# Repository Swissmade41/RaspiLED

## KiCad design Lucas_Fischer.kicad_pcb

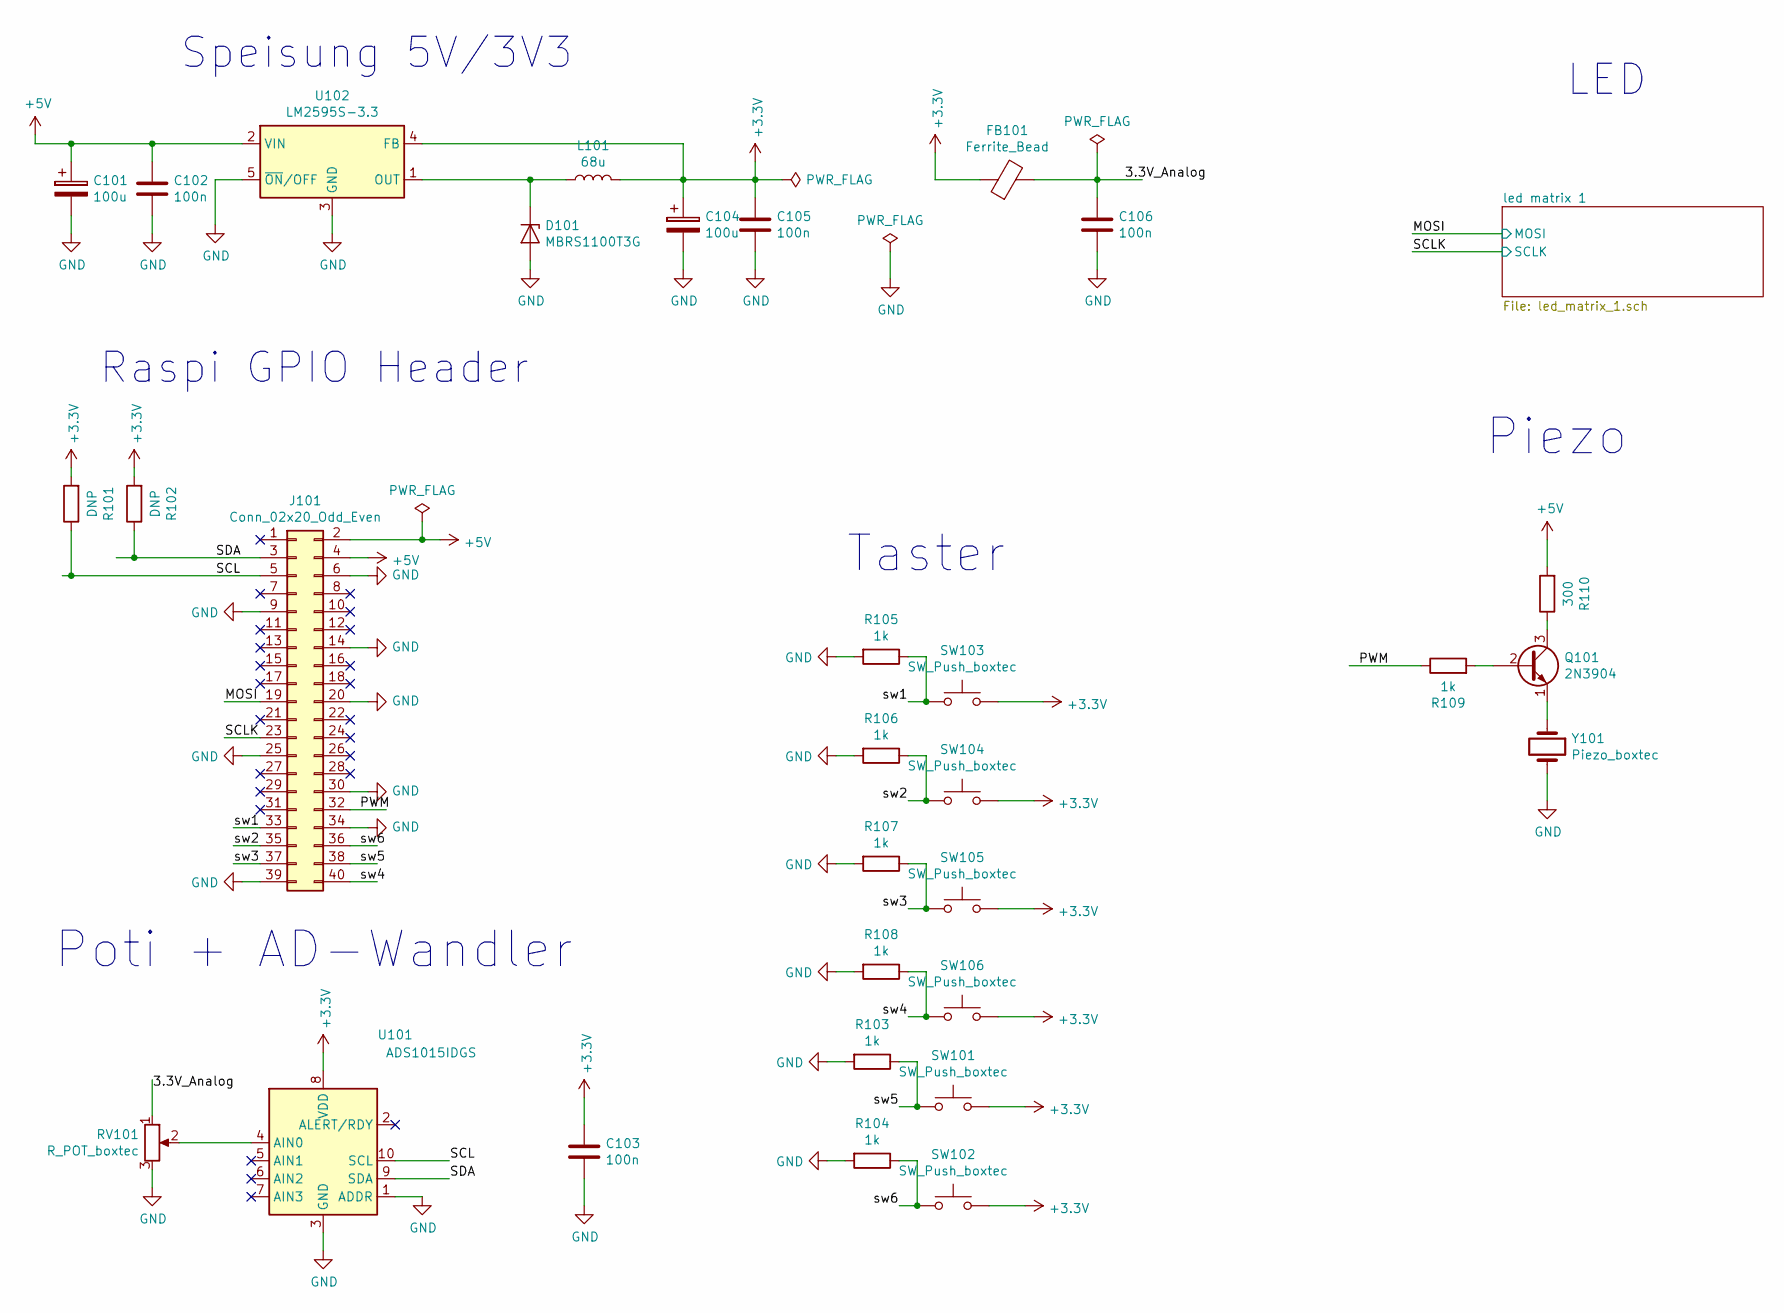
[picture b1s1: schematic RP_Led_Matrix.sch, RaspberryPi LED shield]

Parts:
C101, C104: 100u; CP_Elec_8x6.2
C102, C103, C105, C106: 100n; C_0805_2012Metric
D101: MBRS1100T3G; D_SMB
FB101: Ferrite_Bead; R_0805_2012Metric
J101: Conn_02x20_Odd_Even; PinSocket_2x20_P2.54mm_Vertical
L101: 68u; SDR1006-470KL
Q101: 2N3904; TO-92_Inline
R101, R102: DNP; R_0805_2012Metric
R103, R104, R105, R106, R107, R108, R109: 1k; R_0805_2012Metric
R110: 300; R_0805_2012Metric
RV101: R_POT_boxtec; Potentiometer_Alps_RK09K_Single_Vertical
SW101, SW102, SW103, SW104, SW105, SW106: SW_Push_boxtec; TSA12100TACTSWITCH
U101: ADS1015IDGS; TSSOP-10_3x3mm_P0.5mm
U102: LM2595S-3.3; TO-263-5_TabPin3
Y101: Piezo_boxtec; Piezo CE-C75

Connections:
+3V3: C103.1, C104.1, C105.1, FB101.1, L101.2, R101.2, R102.2, SW101.2, SW102.2, SW103.2, SW104.2, SW105.2, SW106.2, U101.8 (VDD), U102.4 (FB)
+5V: C101.1, C102.1, J101.2, J101.4, R110.2, U102.2 (VIN); also elsewhere on the board
/3.3V_Analog: C106.1, FB101.2, RV101.1
/MOSI: J101.19; also elsewhere on the board
/PWM: J101.32, R109.1
/SCL: J101.5, R101.1, U101.10 (SCL)
/SCLK: J101.23; also elsewhere on the board
/SDA: J101.3, R102.1, U101.9 (SDA)
/sw1: J101.33, R105.1, SW103.1
/sw2: J101.35, R106.1, SW104.1
/sw3: J101.37, R107.1, SW105.1
/sw4: J101.40, R108.1, SW106.1
/sw5: J101.38, R103.1, SW101.1
/sw6: J101.36, R104.1, SW102.1
GND: C101.2, C102.2, C103.2, C104.2, C105.2, C106.2, D101.2 (A), J101.6, J101.9, J101.14, J101.20, J101.25, J101.30, J101.34, J101.39, R103.2, R104.2, R105.2, R106.2, R107.2, R108.2, RV101.3, U101.1 (ADDR), U101.3 (GND), U102.3 (GND), U102.5 (~ON~/OFF), Y101.2; also elsewhere on the board
unnamed: D101.1 (K), L101.1, U102.1 (OUT)
unnamed: Q101.1 (E), Y101.1
unnamed: Q101.2 (B), R109.2
unnamed: Q101.3 (C), R110.1
unnamed: RV101.2, U101.4 (AIN0)

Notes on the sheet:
Raspi GPIO Header
Speisung 5V/3V3
LED
Taster
Poti + AD-Wandler
Piezo

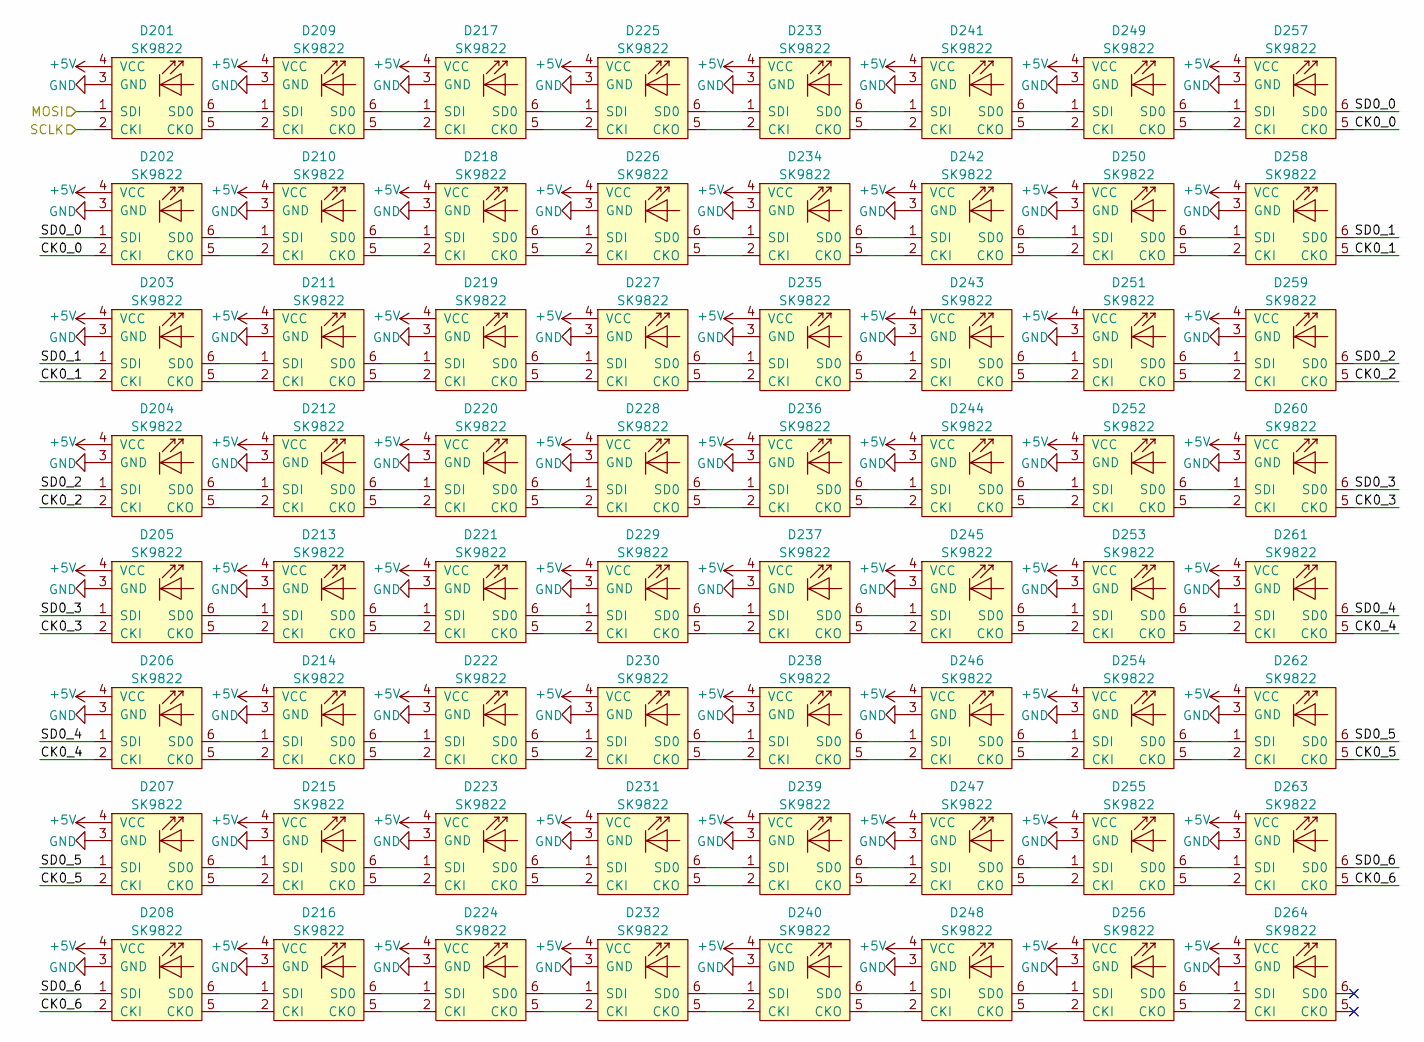
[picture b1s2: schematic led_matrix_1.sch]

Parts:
D201, D202, D203, D204, D205, D206, D207, D208, D209, D210, D211, D212, D213, D214, D215, D216, D217, D218, D219, D220, D221, D222, D223, D224, D225, D226, D227, D228, D229, D230, D231, D232, D233, D234, D235, D236, D237, D238, D239, D240, D241, D242, D243, D244, D245, D246, D247, D248, D249, D250, D251, D252, D253, D254, D255, D256, D257, D258, D259, D260, D261, D262, D263, D264: SK9822

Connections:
+5V: D201.4 (VCC), D202.4 (VCC), D203.4 (VCC), D204.4 (VCC), D205.4 (VCC), D206.4 (VCC), D207.4 (VCC), D208.4 (VCC), D209.4 (VCC), D210.4 (VCC), D211.4 (VCC), D212.4 (VCC), D213.4 (VCC), D214.4 (VCC), D215.4 (VCC), D216.4 (VCC), D217.4 (VCC), D218.4 (VCC), D219.4 (VCC), D220.4 (VCC), D221.4 (VCC), D222.4 (VCC), D223.4 (VCC), D224.4 (VCC), D225.4 (VCC), D226.4 (VCC), D227.4 (VCC), D228.4 (VCC), D229.4 (VCC), D230.4 (VCC), D231.4 (VCC), D232.4 (VCC), D233.4 (VCC), D234.4 (VCC), D235.4 (VCC), D236.4 (VCC), D237.4 (VCC), D238.4 (VCC), D239.4 (VCC), D240.4 (VCC), D241.4 (VCC), D242.4 (VCC), D243.4 (VCC), D244.4 (VCC), D245.4 (VCC), D246.4 (VCC), D247.4 (VCC), D248.4 (VCC), D249.4 (VCC), D250.4 (VCC), D251.4 (VCC), D252.4 (VCC), D253.4 (VCC), D254.4 (VCC), D255.4 (VCC), D256.4 (VCC), D257.4 (VCC), D258.4 (VCC), D259.4 (VCC), D260.4 (VCC), D261.4 (VCC), D262.4 (VCC), D263.4 (VCC), D264.4 (VCC); also elsewhere on the board
/MOSI: D201.1 (SDI); also elsewhere on the board
/SCLK: D201.2 (CKI); also elsewhere on the board
/led matrix 1/CK0_0: D202.2 (CKI), D257.5 (CKO)
/led matrix 1/CK0_1: D203.2 (CKI), D258.5 (CKO)
/led matrix 1/CK0_2: D204.2 (CKI), D259.5 (CKO)
/led matrix 1/CK0_3: D205.2 (CKI), D260.5 (CKO)
/led matrix 1/CK0_4: D206.2 (CKI), D261.5 (CKO)
/led matrix 1/CK0_5: D207.2 (CKI), D262.5 (CKO)
/led matrix 1/CK0_6: D208.2 (CKI), D263.5 (CKO)
/led matrix 1/SD0_0: D202.1 (SDI), D257.6 (SD0)
/led matrix 1/SD0_1: D203.1 (SDI), D258.6 (SD0)
/led matrix 1/SD0_2: D204.1 (SDI), D259.6 (SD0)
/led matrix 1/SD0_3: D205.1 (SDI), D260.6 (SD0)
/led matrix 1/SD0_4: D206.1 (SDI), D261.6 (SD0)
/led matrix 1/SD0_5: D207.1 (SDI), D262.6 (SD0)
/led matrix 1/SD0_6: D208.1 (SDI), D263.6 (SD0)
GND: D201.3 (GND), D202.3 (GND), D203.3 (GND), D204.3 (GND), D205.3 (GND), D206.3 (GND), D207.3 (GND), D208.3 (GND), D209.3 (GND), D210.3 (GND), D211.3 (GND), D212.3 (GND), D213.3 (GND), D214.3 (GND), D215.3 (GND), D216.3 (GND), D217.3 (GND), D218.3 (GND), D219.3 (GND), D220.3 (GND), D221.3 (GND), D222.3 (GND), D223.3 (GND), D224.3 (GND), D225.3 (GND), D226.3 (GND), D227.3 (GND), D228.3 (GND), D229.3 (GND), D230.3 (GND), D231.3 (GND), D232.3 (GND), D233.3 (GND), D234.3 (GND), D235.3 (GND), D236.3 (GND), D237.3 (GND), D238.3 (GND), D239.3 (GND), D240.3 (GND), D241.3 (GND), D242.3 (GND), D243.3 (GND), D244.3 (GND), D245.3 (GND), D246.3 (GND), D247.3 (GND), D248.3 (GND), D249.3 (GND), D250.3 (GND), D251.3 (GND), D252.3 (GND), D253.3 (GND), D254.3 (GND), D255.3 (GND), D256.3 (GND), D257.3 (GND), D258.3 (GND), D259.3 (GND), D260.3 (GND), D261.3 (GND), D262.3 (GND), D263.3 (GND), D264.3 (GND); also elsewhere on the board
unnamed: D201.5 (CKO), D209.2 (CKI)
unnamed: D201.6 (SD0), D209.1 (SDI)
unnamed: D202.5 (CKO), D210.2 (CKI)
unnamed: D202.6 (SD0), D210.1 (SDI)
unnamed: D203.5 (CKO), D211.2 (CKI)
unnamed: D203.6 (SD0), D211.1 (SDI)
unnamed: D204.5 (CKO), D212.2 (CKI)
unnamed: D204.6 (SD0), D212.1 (SDI)
unnamed: D205.5 (CKO), D213.2 (CKI)
unnamed: D205.6 (SD0), D213.1 (SDI)
unnamed: D206.5 (CKO), D214.2 (CKI)
unnamed: D206.6 (SD0), D214.1 (SDI)
unnamed: D207.5 (CKO), D215.2 (CKI)
unnamed: D207.6 (SD0), D215.1 (SDI)
unnamed: D208.5 (CKO), D216.2 (CKI)
unnamed: D208.6 (SD0), D216.1 (SDI)
unnamed: D209.5 (CKO), D217.2 (CKI)
unnamed: D209.6 (SD0), D217.1 (SDI)
unnamed: D210.5 (CKO), D218.2 (CKI)
unnamed: D210.6 (SD0), D218.1 (SDI)
unnamed: D211.5 (CKO), D219.2 (CKI)
unnamed: D211.6 (SD0), D219.1 (SDI)
unnamed: D212.5 (CKO), D220.2 (CKI)
unnamed: D212.6 (SD0), D220.1 (SDI)
unnamed: D213.5 (CKO), D221.2 (CKI)
unnamed: D213.6 (SD0), D221.1 (SDI)
unnamed: D214.5 (CKO), D222.2 (CKI)
unnamed: D214.6 (SD0), D222.1 (SDI)
unnamed: D215.5 (CKO), D223.2 (CKI)
unnamed: D215.6 (SD0), D223.1 (SDI)
unnamed: D216.5 (CKO), D224.2 (CKI)
unnamed: D216.6 (SD0), D224.1 (SDI)
unnamed: D217.5 (CKO), D225.2 (CKI)
unnamed: D217.6 (SD0), D225.1 (SDI)
unnamed: D218.5 (CKO), D226.2 (CKI)
unnamed: D218.6 (SD0), D226.1 (SDI)
unnamed: D219.5 (CKO), D227.2 (CKI)
unnamed: D219.6 (SD0), D227.1 (SDI)
unnamed: D220.5 (CKO), D228.2 (CKI)
unnamed: D220.6 (SD0), D228.1 (SDI)
unnamed: D221.5 (CKO), D229.2 (CKI)
unnamed: D221.6 (SD0), D229.1 (SDI)
unnamed: D222.5 (CKO), D230.2 (CKI)
unnamed: D222.6 (SD0), D230.1 (SDI)
unnamed: D223.5 (CKO), D231.2 (CKI)
unnamed: D223.6 (SD0), D231.1 (SDI)
unnamed: D224.5 (CKO), D232.2 (CKI)
unnamed: D224.6 (SD0), D232.1 (SDI)
unnamed: D225.5 (CKO), D233.2 (CKI)
unnamed: D225.6 (SD0), D233.1 (SDI)
unnamed: D226.5 (CKO), D234.2 (CKI)
unnamed: D226.6 (SD0), D234.1 (SDI)
unnamed: D227.5 (CKO), D235.2 (CKI)
unnamed: D227.6 (SD0), D235.1 (SDI)
unnamed: D228.5 (CKO), D236.2 (CKI)
unnamed: D228.6 (SD0), D236.1 (SDI)
unnamed: D229.5 (CKO), D237.2 (CKI)
unnamed: D229.6 (SD0), D237.1 (SDI)
unnamed: D230.5 (CKO), D238.2 (CKI)
unnamed: D230.6 (SD0), D238.1 (SDI)
unnamed: D231.5 (CKO), D239.2 (CKI)
unnamed: D231.6 (SD0), D239.1 (SDI)
unnamed: D232.5 (CKO), D240.2 (CKI)
unnamed: D232.6 (SD0), D240.1 (SDI)
unnamed: D233.5 (CKO), D241.2 (CKI)
unnamed: D233.6 (SD0), D241.1 (SDI)
unnamed: D234.5 (CKO), D242.2 (CKI)
unnamed: D234.6 (SD0), D242.1 (SDI)
unnamed: D235.5 (CKO), D243.2 (CKI)
unnamed: D235.6 (SD0), D243.1 (SDI)
unnamed: D236.5 (CKO), D244.2 (CKI)
unnamed: D236.6 (SD0), D244.1 (SDI)
unnamed: D237.5 (CKO), D245.2 (CKI)
unnamed: D237.6 (SD0), D245.1 (SDI)
unnamed: D238.5 (CKO), D246.2 (CKI)
unnamed: D238.6 (SD0), D246.1 (SDI)
unnamed: D239.5 (CKO), D247.2 (CKI)
unnamed: D239.6 (SD0), D247.1 (SDI)
unnamed: D240.5 (CKO), D248.2 (CKI)
unnamed: D240.6 (SD0), D248.1 (SDI)
unnamed: D241.5 (CKO), D249.2 (CKI)
unnamed: D241.6 (SD0), D249.1 (SDI)
unnamed: D242.5 (CKO), D250.2 (CKI)
unnamed: D242.6 (SD0), D250.1 (SDI)
unnamed: D243.5 (CKO), D251.2 (CKI)
unnamed: D243.6 (SD0), D251.1 (SDI)
unnamed: D244.5 (CKO), D252.2 (CKI)
unnamed: D244.6 (SD0), D252.1 (SDI)
unnamed: D245.5 (CKO), D253.2 (CKI)
unnamed: D245.6 (SD0), D253.1 (SDI)
unnamed: D246.5 (CKO), D254.2 (CKI)
unnamed: D246.6 (SD0), D254.1 (SDI)
unnamed: D247.5 (CKO), D255.2 (CKI)
unnamed: D247.6 (SD0), D255.1 (SDI)
unnamed: D248.5 (CKO), D256.2 (CKI)
unnamed: D248.6 (SD0), D256.1 (SDI)
unnamed: D249.5 (CKO), D257.2 (CKI)
unnamed: D249.6 (SD0), D257.1 (SDI)
unnamed: D250.5 (CKO), D258.2 (CKI)
unnamed: D250.6 (SD0), D258.1 (SDI)
unnamed: D251.5 (CKO), D259.2 (CKI)
unnamed: D251.6 (SD0), D259.1 (SDI)
unnamed: D252.5 (CKO), D260.2 (CKI)
unnamed: D252.6 (SD0), D260.1 (SDI)
unnamed: D253.5 (CKO), D261.2 (CKI)
unnamed: D253.6 (SD0), D261.1 (SDI)
unnamed: D254.5 (CKO), D262.2 (CKI)
unnamed: D254.6 (SD0), D262.1 (SDI)
unnamed: D255.5 (CKO), D263.2 (CKI)
unnamed: D255.6 (SD0), D263.1 (SDI)
unnamed: D256.5 (CKO), D264.2 (CKI)
unnamed: D256.6 (SD0), D264.1 (SDI)

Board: 4 copper layers, 99 parts (0 on the bottom side), 146 nets, no tracks yet.

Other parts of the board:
H1, H2, H3, H4: MountingHole_Pad; MountingHole_3.2mm_M3

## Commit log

2019-03-13 upload
2019-03-27 update Schema
    -pwr flag eingefügt
    -3.3V Analog Netzleibel eingefügt
2019-03-27 update schema
    -MISO to MOSI
2019-04-10 Update Schema
    Footprint
    Netlist
2019-04-12 mii shit
